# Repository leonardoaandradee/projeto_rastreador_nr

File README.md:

# projeto_rastreador_nr
Projeto de um rastreador GPS de cargas com sensor de temperatura  embutido.

#link para gitpage: https://leonardoaandradee.github.io/projeto_rastreador_nr/

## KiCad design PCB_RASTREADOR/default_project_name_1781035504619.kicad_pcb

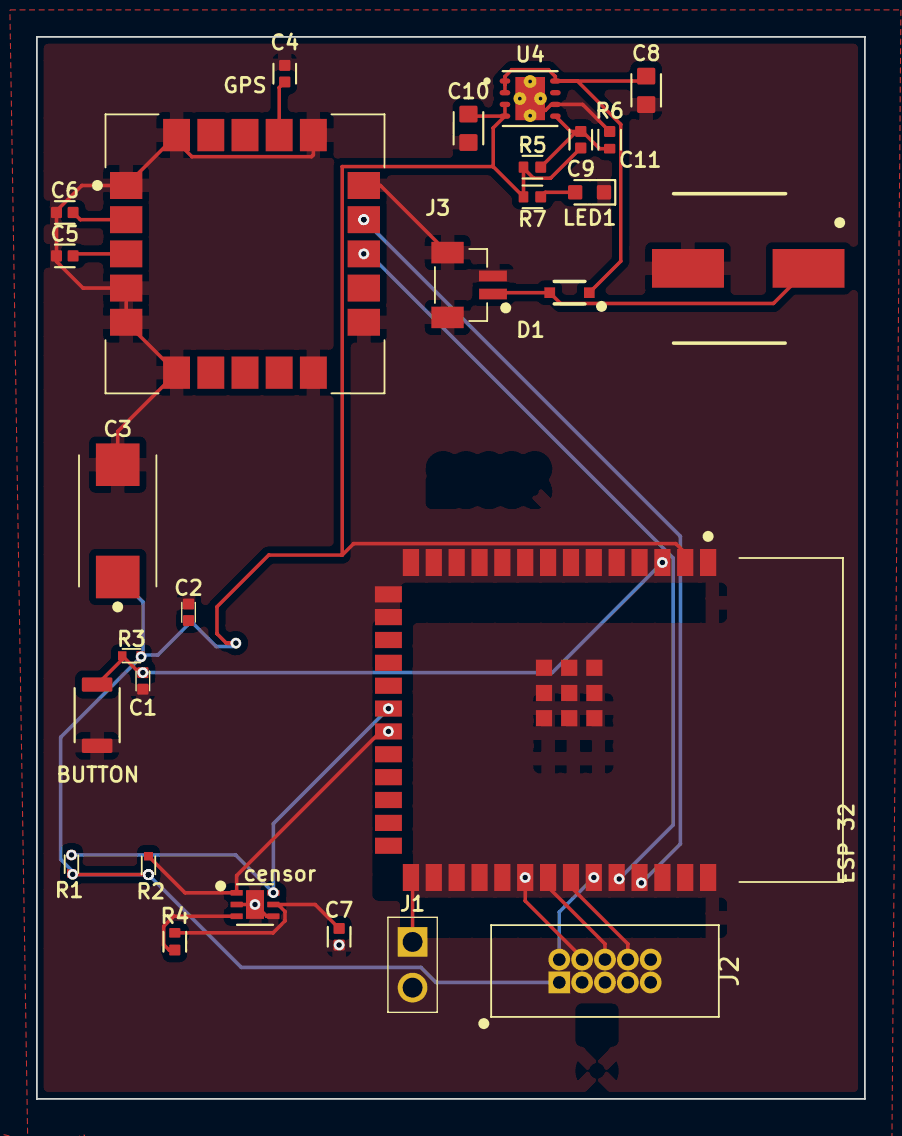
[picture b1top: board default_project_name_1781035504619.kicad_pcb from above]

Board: 2 copper layers, 46.0 x 59.0 mm, 28 parts (0 on the bottom side), 21 nets.

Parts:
BUTTON: B3U-1000P
C1, C2: KGM05CR71H104KH
C3: T491D107K016AT
C4, C5, C6: GCM155R71C104KA55D
C7: KGM05AR51E104KH
C8, C10: CC0603KRX7R6BB225
C9: CC0402JRNPO9BN150
C11: UUR0J471MNL1GS
D1: PMEG4005EJF
ESP 32: ESP32-S3-WROOM-1-N8R2
GPS: SAM-M10Q-00B
J1: 61300211121
J2: 3220-10-0100-00
J3: 665302124022
LED1: LTST-C191KRKT
R1, R2, R3: ERJ2RKF1002X
R4: ERJ2RKF5101X
R5: ERJ2GEJ513X
R6: ERJ2RKF3002X
R7: ERJ2RKF6800X
U4: TPS79601DRBR
censor: TMP117MAIDRVR

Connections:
/RXD0: ESP 32.36, GPS.13
/SCL: ESP 32.21, R2.1, censor.1
/SDA: ESP 32.20, R1.1, censor.6
/TXD0: ESP 32.37, GPS.14
/sheet_3_Temperature/ALERT: R4.1, censor.3
GND: BUTTON.1, C1.2, C2.2, C3.2, C4.2, C5.2, C6.2, C7.2, C8.2, C10.2, C11.2, ESP 32.1, ESP 32.40, ESP 32.41, ESP 32.42, ESP 32.43, ESP 32.44, ESP 32.45, ESP 32.46, ESP 32.47, ESP 32.48, ESP 32.49, GPS.1, GPS.4, GPS.5, GPS.6, GPS.10, GPS.11, GPS.15, GPS.16, GPS.20, J1.2, J2.3, J2.5, J2.9, J3.2, J3.3, J3.4, LED1.K, R6.1, U4.6, U4.9, censor.2, censor.4, censor.7
unnamed: C11.1, D1.2, J3.1
unnamed: LED1.A, R7.1
unnamed: BUTTON.2, C1.1, ESP 32.3, R3.1
unnamed: ESP 32.27, J1.1
unnamed: ESP 32.32, J2.4
unnamed: ESP 32.33, J2.6
unnamed: ESP 32.34, J2.8
unnamed: ESP 32.35, J2.2
unnamed: C9.2, R5.1, R6.2, U4.5
VBAT: C8.1, D1.1, U4.1, U4.2, U4.8
VBCKP: C5.1, GPS.3
VCC: C2.1, C3.1, C9.1, C10.1, ESP 32.2, J2.1, R1.2, R2.2, R3.2, R5.2, R7.2, U4.3, U4.4
VCC_1: C4.1, GPS.17
VCC_2: C7.1, R4.2, censor.5
VDDIO: C6.1, GPS.2

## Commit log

2026-04-07 Primeira versão da gitpage do projeto do rastreador
2026-04-07 Add GitHub Pages link to README
    Added a link to the GitHub Pages site for the project.
2026-06-02 Estrutura base do pra nuvem
2026-06-02 Configurando banco de dados em nuvem com variaveis de ambiente
2026-06-02 Gerando migrations da tabela de caminhoes
2026-06-03 Migration definitiva da tabela mqtt_users
2026-06-09 adicionado o OTA
2026-06-11 Adição de fotos do produto final, pcb etc...
2026-06-17 Atualizado o link do código fonte no index.html
2026-06-17 tinha colocado o link errado
